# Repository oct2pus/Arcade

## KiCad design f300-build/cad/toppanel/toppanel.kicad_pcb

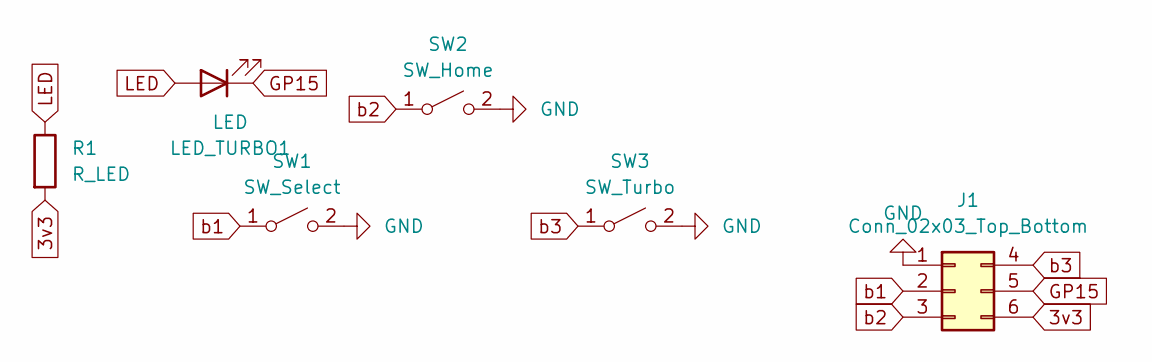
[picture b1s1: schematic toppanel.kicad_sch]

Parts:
J1: Conn_02x03_Top_Bottom; PinHeader_1x06_P1.00mm_Horizontal
LED_TURBO1: LED; LED_D5.0mm
R1: R_LED; R_Axial_DIN0207_L6.3mm_D2.5mm_P7.62mm_Horizontal
SW1: SW_Select; membrane_button
SW2: SW_Home; membrane_button
SW3: SW_Turbo; membrane_button

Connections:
3v3: J1.6, R1.2
GND: J1.1, SW1.2 (B), SW2.2 (B), SW3.2 (B)
GP15: J1.5, LED_TURBO1.1 (K)
LED: LED_TURBO1.2 (A), R1.1
b1: J1.2, SW1.1 (A)
b2: J1.3, SW2.1 (A)
b3: J1.4, SW3.1 (A)

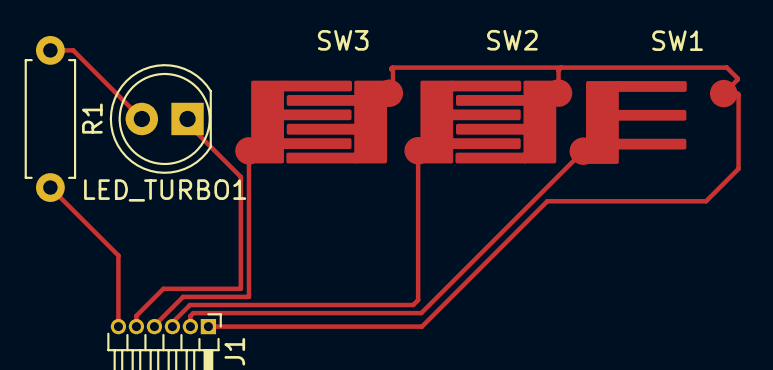
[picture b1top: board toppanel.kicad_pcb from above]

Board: 2 copper layers, 6 parts (0 on the bottom side), 7 nets.

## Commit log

2022-05-13 begin work on a fightstick
2022-05-13 remove unneccessary files
2022-05-13 add shaft cover, group consts
2022-05-13 ignore .dxf files
2022-05-19 lol tornado
2022-05-21 lol thunderstorm
2022-05-23 v0.9 (the usb port is still slightly off)
2022-05-25 add test scaffolding for height and pegholes
2022-05-31 modify screw diameters, new bottom thickness, new renderer
2022-05-31 remove commented out code, move test functions to tests.go
2022-05-31 update sdfx version in arcade
2022-05-31 remove commented out code
2022-05-31 move (and vastly simplify) peg placement on plate
2022-05-31 let tests.go actually compile lol
2022-06-02 simplify main.go
2022-06-02 minor spacing change
2022-06-02 add a keycap model
2022-06-02 switch back to 3 for m3 screw
2022-06-02 add keyswitch to the compile
2022-06-02 update binary
2022-06-02 remove some commented out code
2022-06-02 move control stick parts to stick parts
2022-06-02 rename hjklbox to Hey! JKL
2022-06-02 change Hey! JKL to Hey!JKL
2022-06-02 change hjklbox to Hey! JKL
2022-06-02 clean up on aisle 5
2022-06-11 move functions out of top, minor tweaks
2022-06-11 use dc renderer
2022-06-11 body.go -> base.go
2022-06-11 rows.go -> clusters.go, change sdf.V2 to v2.Vec
2022-06-11 add trapezoid()
2022-06-11 rough version of wallsPlane()
2022-06-12 thin wall thickness, create indents in wall because its cute
2022-06-12 move split planes off into planes.go
2022-06-12 use plane for render splitting
2022-06-12 upd8!!!!!!!!
2022-06-17 thin wall, add protrosions for screws, remove function row,
2022-06-17 planes -> parts, expand parts
2022-06-17 slightly higher resolution DXF files
2022-06-17 remove auxillary buttons from top, begin work on mounting holes
2022-06-30 recover split2DPlane and split3DModel from parts.go
2022-06-30 add lil trapezoids to the corners of the walls, move screws a lil
2022-06-30 remove parts.go because it was over complicating things lol
2022-06-30 fix a silly little error :3
2022-06-30 add a bottom lol
2022-06-30 remove an svg
2022-06-30 create box64 (to be worked on)
2022-06-30 body.go -> body2D.go, create body3D.go
2022-06-30 remove a comment
2022-06-30 add a nice lil newline to .gitignore
2022-06-30 god please stop reminding me about top.dxf
2022-07-01 add wallCorner()
2022-07-01 model out wallcorners
2022-07-01 render new models
2022-07-03 correct wallCorner's comment.
2022-07-03 rotate wallFrontRight
2022-07-03 rotate wallFrontLeft
2022-07-03 rotate wallBackRight
2022-07-03 rotate wallBackLeft
2022-07-03 remove TODOs
2022-07-03 add innerWallPlane
2022-07-03 remove pointless variable
2022-07-03 thicken inner wall
2022-07-03 add innerWall, move wallcorner to body3d, rerotate walls
2022-07-03 update renders
2022-07-05 include a (commented out) test for hole sizes/neutrik
2022-07-05 move neutrk to clusters, correct neutrik orientation
2022-07-05 add a neutrik ref
2022-07-05 compliation
2022-07-07 move wallCorner, remove todos.
2022-07-07 move screwHoles() to clusters.go
2022-07-07 remove a test render
2022-07-07 add countersinkTest.go
2022-07-07 update bin
2022-07-08 fix length of inner wall ends
2022-07-08 start (and abandon) countersunk screws
2022-07-08 fix split3DModel()
2022-07-15 add stickMountTest
2022-07-18 start work on arcade!shark
2022-07-19 add mounting holes to ablzrSwitchHolder
2022-07-20 expand switch hole, shrink button insert
2022-07-21 add stand-offs to switch holder
2022-07-21 added pegs to minimize button wobble
2022-07-22 remove comment
2022-07-22 use a const
2022-07-22 dpad done
2022-08-21 push 3d printed parts for f300 build
2022-08-21 initial PCB design for f300 replacement control panel
2022-08-24 added usbCMount and usbCCover
2022-09-03 create sanwa-caps
2022-09-03 finish f300-build
2022-09-04 modify tolerances for cap
2022-10-30 add plugs
2022-11-26 modifications to stickparts and arcade shark
2023-02-03 choc buttons take 1
2023-02-03 forgot i fixed the 0.75 mm discrepency
